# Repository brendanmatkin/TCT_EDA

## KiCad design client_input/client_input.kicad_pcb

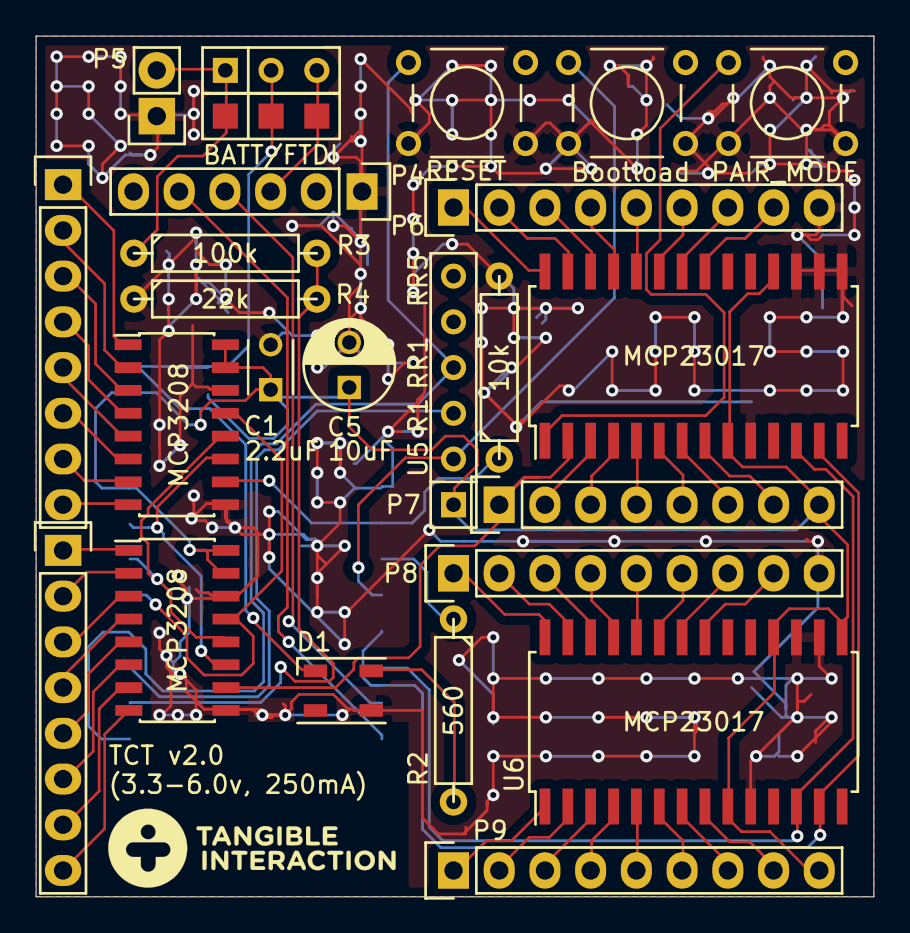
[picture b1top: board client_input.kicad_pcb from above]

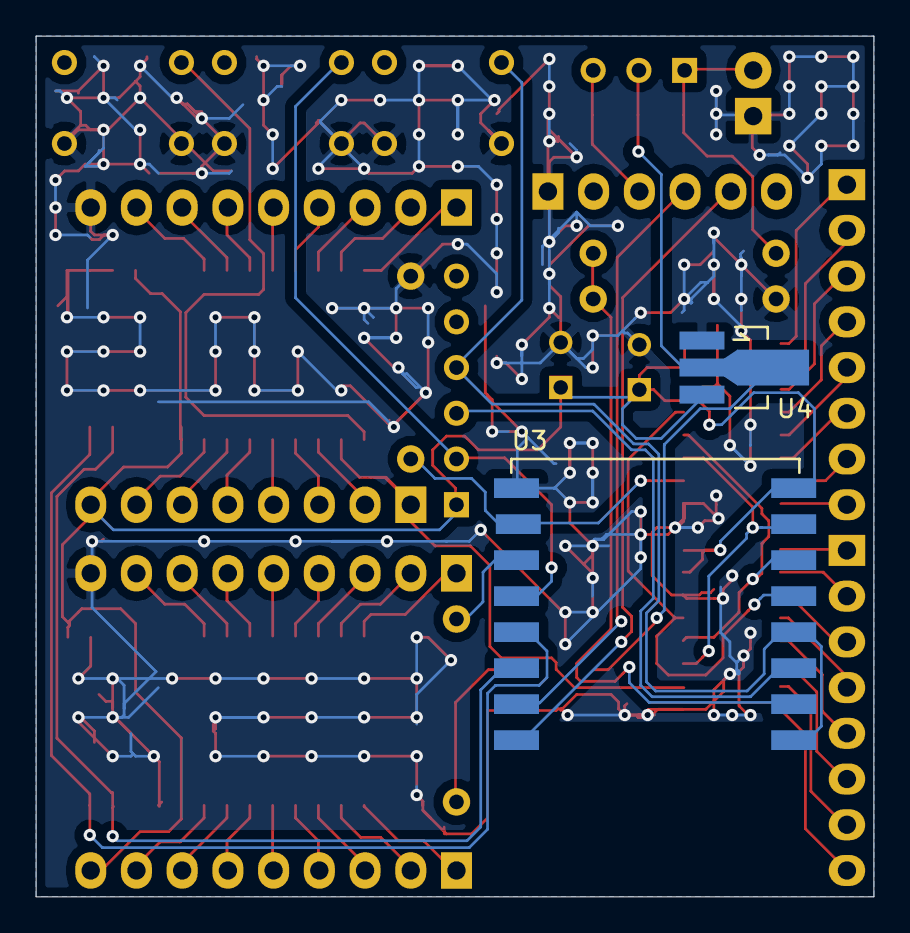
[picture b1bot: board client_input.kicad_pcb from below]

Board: 2 copper layers, 46.5 x 47.8 mm, 26 parts (2 on the bottom side), 67 nets.

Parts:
C1: 2.2uF; C_Disc_D3_P2.5
C5: 10uF; C_Radial_D5_L6_P2.5
D1: WS2812B; LED_NEOPIXEL
P1, P2: Analog In; Socket_Strip_Straight_1x08
P4: FTDI; Pin_Header_Straight_1x06
P5: LiPo; Socket_Strip_Straight_1x02
P6, P8, P9: Ribbon; Socket_Strip_Straight_1x09
P7: Ribbon; Socket_Strip_Straight_1x08
R1: 10k; R4
R2: 560; R4
R3: 100k; R4
R4: 22k; R4
RR1: RR5; Resistor_Array_SIP5
SW1: RESET; SW_PUSH_SMALL
SW2: PAIR_MODE; SW_PUSH_SMALL
SW3: Bootload; SW_PUSH_SMALL
SW5: SPDT; SW_Micro_SPST
U1, U2: MCP3208; SOIC-16_3.9x9.9mm_Pitch1.27mm
U3: ESP-12E; ESP-12E_Brendan
U4: MCP1700-3302; SOT89-3_Housing_Handsoldering
U5, U6: MCP23017; SOIC-28_7.5x17.9mm_Pitch1.27mm

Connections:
+3V3: C1.1, C5.1, P7.8, P9.9, RR1.1, U1.15, U1.16, U2.15, U2.16, U3.8, U4.3, U5.9, U5.18, U6.9, U6.15, U6.18
+BATT: P5.2, R3.1, SW5.1
+Vin: D1.1, SW5.2, U4.2
BL_sw: RR1.2, SW3.1, U3.12
BattSense: R3.2, R4.2, U3.2
CH_PD: RR1.3, U3.3
FTDI_VCC: P4.3, SW5.3
GND: C1.2, C5.2, D1.3, P4.1, P5.1, P6.9, P8.9, R1.2, R4.1, SW1.2, SW2.2, SW3.2, U1.9, U1.14, U2.9, U2.14, U3.9, U4.1, U5.10, U5.15, U5.16, U5.17, U6.10, U6.16, U6.17
LED_stat: R2.1, U3.11
MISO: U1.12, U2.12, U3.6
MOSI: U1.11, U2.11, U3.7
unnamed: D1.4, R2.2
unnamed: P1.1, U1.1
unnamed: P1.2, U1.2
unnamed: P1.3, U1.3
unnamed: P1.4, U1.4
unnamed: P1.5, U1.5
unnamed: P1.6, U1.6
unnamed: P1.7, U1.7
unnamed: P1.8, U1.8
unnamed: P2.1, U2.1
unnamed: P2.2, U2.2
unnamed: P2.3, U2.3
unnamed: P2.4, U2.4
unnamed: P2.5, U2.5
unnamed: P2.6, U2.6
unnamed: P2.7, U2.7
unnamed: P2.8, U2.8
unnamed: P4.4, U3.15
unnamed: P4.5, U3.16
unnamed: P6.1, U5.28
unnamed: P6.2, U5.27
unnamed: P6.3, U5.26
unnamed: P6.4, U5.25
unnamed: P6.5, U5.24
unnamed: P6.6, U5.23
unnamed: P6.7, U5.22
unnamed: P6.8, U5.21
unnamed: P7.1, U2.10, U5.2
unnamed: P7.2, U5.3
unnamed: P7.3, U5.4
unnamed: P7.4, U5.5
unnamed: P7.5, U5.6
unnamed: P7.6, U5.7
unnamed: P7.7, U5.8
unnamed: P8.1, U6.28
unnamed: P8.2, U6.27
unnamed: P8.3, U6.26
unnamed: P8.4, U6.25
unnamed: P8.5, U6.24
unnamed: P8.6, U6.23
unnamed: P8.7, U6.22
unnamed: P8.8, U6.21
unnamed: P9.1, U6.1
unnamed: P9.2, U6.2
unnamed: P9.3, U6.3
unnamed: P9.4, U6.4
unnamed: P9.5, U6.5
unnamed: P9.6, U6.6
unnamed: P9.7, U6.7
unnamed: P9.8, U6.8
Pair_sw: SW2.1, U5.1
RST: RR1.4, SW1.1, U3.1, U3.4
SCL: U3.14, U5.12, U6.12
SDA: U3.13, U5.13, U6.13
SPI_CLK: U1.13, U2.13, U3.5
SPI_SS: R1.1, U1.10, U3.10

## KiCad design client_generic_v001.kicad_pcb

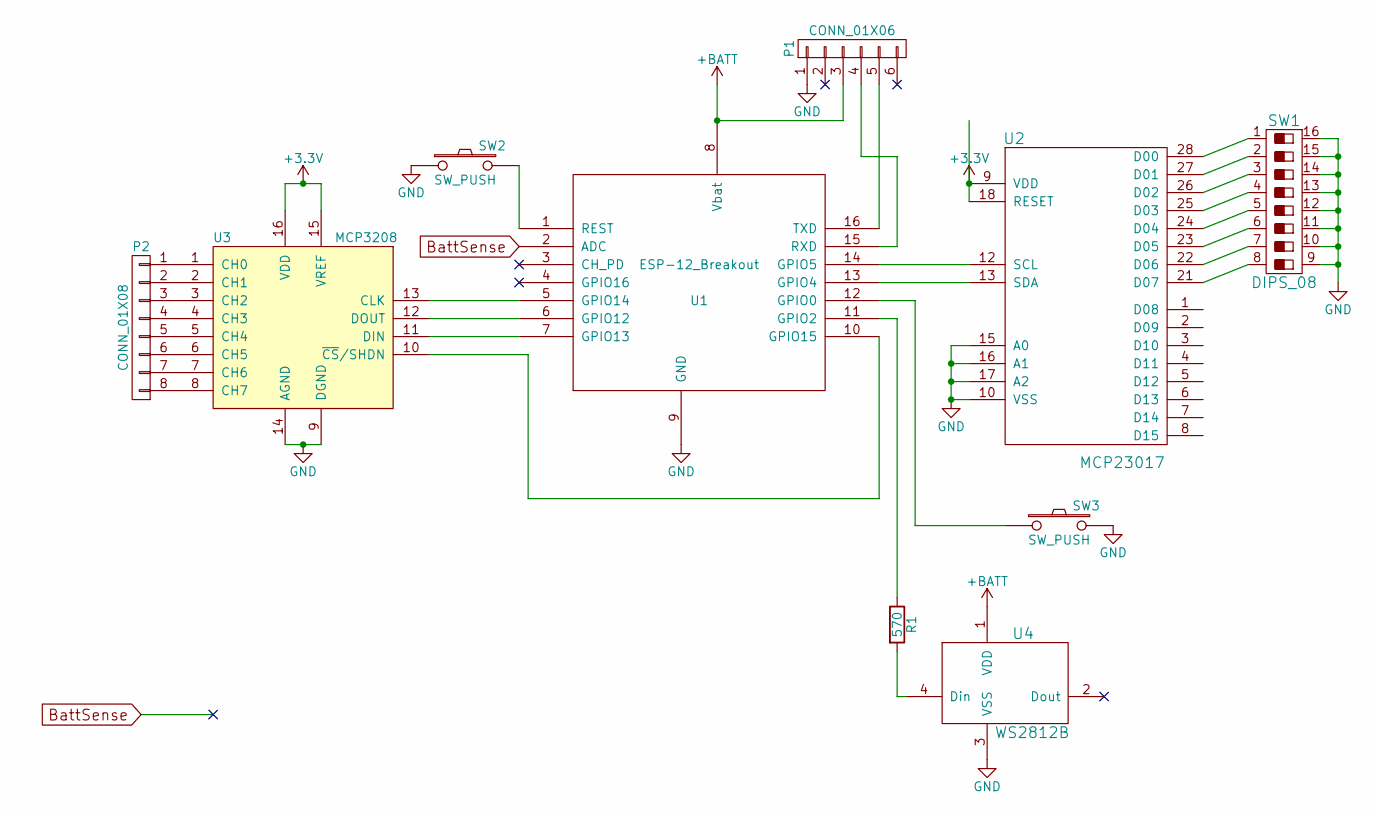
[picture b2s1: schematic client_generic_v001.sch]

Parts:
P1: CONN_01X06; Pin_Header_Angled_1x06
P2: CONN_01X08; Socket_Strip_Straight_1x08
R1: 570; Resistor_Horizontal_RM10mm
SW1: DIPS_08; SW_DIP_x8_Slide
SW2, SW3: SW_PUSH; SW_TH_Tactile_Omron_B3F-10xx
U1: ESP-12_Breakout; ESP12_Breakout
U2: MCP23017; DIP-28_W7.62mm_LongPads
U3: MCP3208; DIP-18_W7.62mm_LongPads
U4: WS2812B; LED_RGB_PLLC-6

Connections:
+3V3: U2.9 (VDD), U2.18 (RESET), U3.15 (VREF), U3.16 (VDD)
+BATT: P1.3, U1.8 (Vbat), U4.1 (VDD)
BattSense: U1.2 (ADC)
GND: P1.1, SW1.9, SW1.10, SW1.11, SW1.12, SW1.13, SW1.14, SW1.15, SW1.16, SW2.1, SW3.2, U1.9 (GND), U2.10 (VSS), U2.15 (A0), U2.16 (A1), U2.17 (A2), U3.9 (DGND), U3.14 (AGND), U4.3 (VSS)
unnamed: P1.4, U1.15 (RXD)
unnamed: P1.5, U1.16 (TXD)
unnamed: P2.1, U3.1 (CH0)
unnamed: P2.2, U3.2 (CH1)
unnamed: P2.3, U3.3 (CH2)
unnamed: P2.4, U3.4 (CH3)
unnamed: P2.5, U3.5 (CH4)
unnamed: P2.6, U3.6 (CH5)
unnamed: P2.7, U3.7 (CH6)
unnamed: P2.8, U3.8 (CH7)
unnamed: R1.1, U1.11 (GPIO2)
unnamed: R1.2, U4.4 (Din)
unnamed: SW1.1, U2.28 (D00)
unnamed: SW1.2, U2.27 (D01)
unnamed: SW1.3, U2.26 (D02)
unnamed: SW1.4, U2.25 (D03)
unnamed: SW1.5, U2.24 (D04)
unnamed: SW1.6, U2.23 (D05)
unnamed: SW1.7, U2.22 (D06)
unnamed: SW1.8, U2.21 (D07)
unnamed: SW2.2, U1.1 (REST)
unnamed: SW3.1, U1.12 (GPIO0)
unnamed: U1.5 (GPIO14), U3.13 (CLK)
unnamed: U1.6 (GPIO12), U3.12 (DOUT)
unnamed: U1.7 (GPIO13), U3.11 (DIN)
unnamed: U1.10 (GPIO15), U3.10 (~CS~/SHDN)
unnamed: U1.13 (GPIO4), U2.13 (SDA)
unnamed: U1.14 (GPIO5), U2.12 (SCL)

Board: 2 copper layers, 10 parts (0 on the bottom side), 31 nets, no tracks yet.

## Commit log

2016-07-08 initial commit - first pass at: schematic, footprints, netlist, and pcb layout
2016-07-08 Added status LEDs
2016-07-08 minor tweaks to schematic + RENAMED ALL FILES
2016-07-08 rename (again)
2016-07-08 updated references, added BattSense, fixed errors
2016-07-08 add RGB status LED alternative
2016-07-08 PCD laid out.
2016-07-25 Made some tweaks, outputted test gerber files (still PTH version).
2016-08-06 version 2.0, lots of changes. (smd parts, 2 sided, production ready)
2016-08-06 totally screwed up stitching vias and then fixed them
2016-08-06 finished re-doing stitching vias
2016-08-10 Nearly ready to go 2 sided. ESP + reg on back, rest on front. Stitched ground planes. Needs: some ground plane gaps filled, add some caps.
2016-08-11 improved ground planes and re-worked stitching-vias
2016-08-13 Final revisions, exports, panelization, and gerbers for Rev 2. Sent to Elecrow (11 August 2016).
